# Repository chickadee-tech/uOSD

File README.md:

# Chickadee Tech Acro Polystack Mod #
This mod cradles a MicroMinimOSD and connects it to the base control board.

## Documentation ##
See the [wiki](https://github.com/chickadee-tech/uOSD/wiki) for documentation.

## Polystack ##
This **mod** board is part of the Polystack platform for modular microcontrol systems. More information on the platform can be found at [polystack.org](http://polystack.org).

## Support ##
If you need support with a board you own or have development questions please email support@chickadee.tech or check [chickadee.tech/support](https://chickadee.tech/support) for other ways to get support.

## Contributing ##
Please note that this project is released with a [Contributor Code of Conduct](CODE_OF_CONDUCT.md). By participating in this project you agree to abide by its terms.

### Setup ###
Components and footprints for PCB parts are not included in this repository. Instead, checkout the [chickadee-tech/kicad-libs](https://github.com/chickadee-tech/kicad-libs) repository in the same directory that this repository is checked out in. All part definitions should be relative so that they will load correctly.

### Pull requests ###
For fixes please submit a pull request to the original repository. After the pull request is merged, check the [Chickadee Tech Active Contributor Discount (ACD)](https://chickadee.tech/active-contributor) to see if you are eligible for a discount code to use on your next purchase.

### Derivatives ###
If developing your own version of the MicroMinimOSD cradle board please remove all Chickadee Tech trademarks and follow the [CC-BY license](LICENSE). While not required, please consider open sourcing your modifications so others can learn from your improvements. If you do email support@chickadee.tech and we may choose to add your project to the ACD.

You may also license the Polystack logo for free by emailing support@chickadee.tech. We'll ask for your gerbers to ensure the design complies with specifications laid out [here](https://github.com/chickadee-tech/polystack/wiki) and provide written permission to use the trademark after compliance has been demonstrated.

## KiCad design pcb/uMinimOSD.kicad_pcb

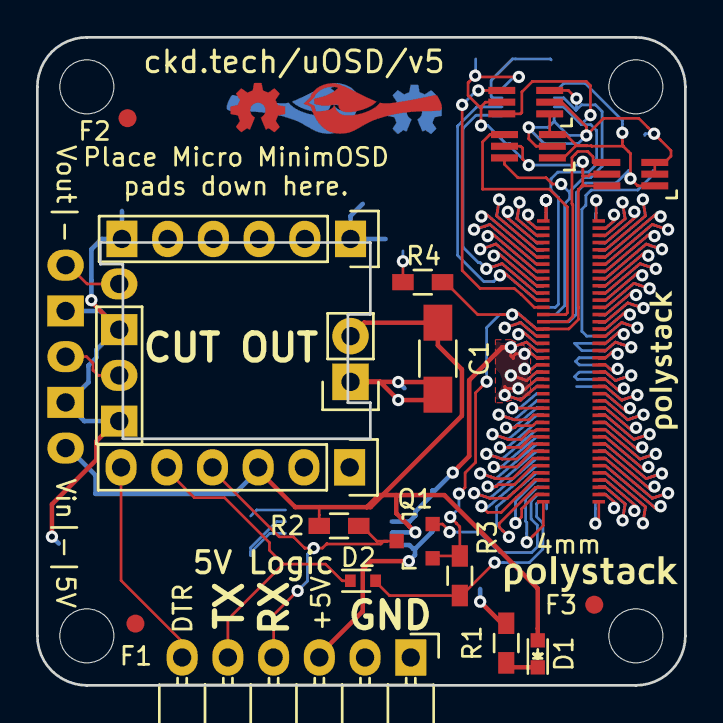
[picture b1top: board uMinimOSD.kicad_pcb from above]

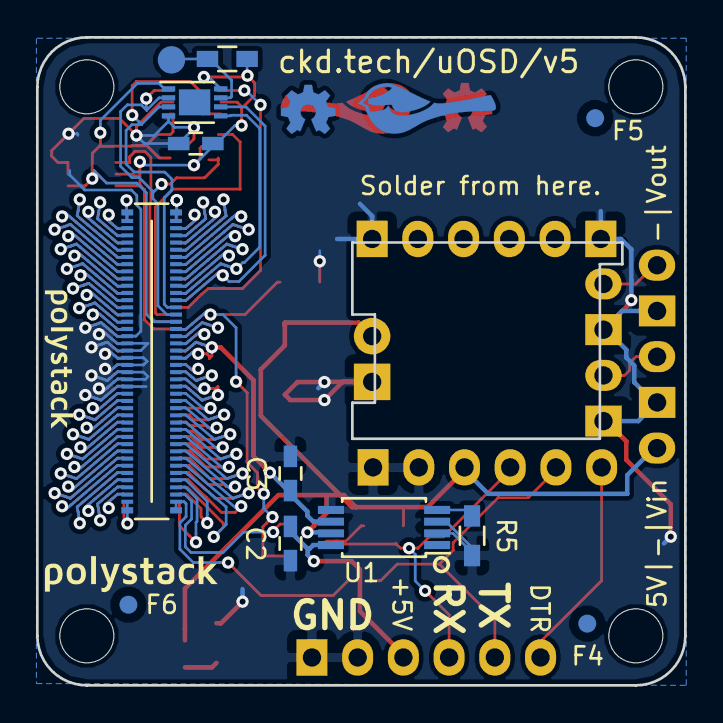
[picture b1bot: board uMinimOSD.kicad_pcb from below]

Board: 2 copper layers, 36.0 x 36.0 mm, 37 parts (14 on the bottom side), 81 nets.

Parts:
C1: 10uF; C_1206_HandSoldering
C2, C3: 0.1uF; C_0603_HandSoldering
D1: Red; LED-0603
D2: RB751S40; SOD-523
F1, F2, F3, F4, F5, F6: 1mm; Fiducial
P1: CONN_01X05; Pin_Header_Straight_1x05
P2: CONN_01X04; Pin_Header_Straight_1x04
P3, P4: CONN_01X06; Pin_Header_Straight_1x06
P5: CONN_01X02; Pin_Header_Straight_1x02
P6: CONN_01X06; Pin_Header_Angled_1x06
PORT_ANDOR1: SN74LVC1G0832; SC-70-6_Handsoldering
PORT_C1: 0.1uF; C_0603_HandSoldering
PORT_IC1: AT24CS02-MAHM; DFN-8-1EP_3x2mm_Pitch0.5mm
PORT_IN1: CKD_SANDWICH; DF40-80pin-Header
PORT_INV1: SN74LVC1G58; SC-70-6_Handsoldering
PORT_OUT1: CKD_SANDWICH; DF40-3-4mm-80pin-Receptacle
PORT_P1: CONN_01X01; Measurement_Point_Round-SMD-Pad_Small
PORT_R1: 10k; R_0603_HandSoldering
PORT_XOR1: SN74LVC1G58; SC-70-6_Handsoldering
Q1: Q_NMOS_GSD; SOT-23
R1: 1k; R_0603_HandSoldering
R2, R3, R4: 10k; R_0603_HandSoldering
R5: 470; R_0603_HandSoldering
U1: TPS2112; TSSOP-8_4.4x3mm_Pitch0.65mm
svg2mod, svg2mod#2: G***; polystack-bold-0.5
svg2mod#3, svg2mod#4: G***; polystack-bold-0.4

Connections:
+3V3: PORT_ANDOR1.5, PORT_C1.1, PORT_IC1.8, PORT_IN1.16, PORT_INV1.5, PORT_INV1.6, PORT_OUT1.16, PORT_R1.2, PORT_XOR1.5, Q1.1, R3.1, R4.1
+5V: C1.1, D1.2, P1.1, P3.3, P5.2, R2.1, U1.7
/DTR: P3.6, P6.6
/ExpansionPort/3V3_0.3A_E: PORT_IN1.17, PORT_OUT1.17
/ExpansionPort/+BATT: PORT_IN1.18, PORT_OUT1.18
/ExpansionPort/ADC1: PORT_IN1.49, PORT_OUT1.49
/ExpansionPort/ADC2: PORT_IN1.50, PORT_OUT1.50
/ExpansionPort/BOOT: PORT_IN1.65, PORT_OUT1.65
/ExpansionPort/CAN_HI: PORT_IN1.67, PORT_OUT1.67
/ExpansionPort/CAN_LO: PORT_IN1.68, PORT_OUT1.68
/ExpansionPort/FS_5V: C3.1, PORT_IN1.19, PORT_IN1.20, PORT_IN1.21, PORT_IN1.22, PORT_IN1.23, PORT_IN1.24, PORT_OUT1.19, PORT_OUT1.20, PORT_OUT1.21, PORT_OUT1.22, PORT_OUT1.23, PORT_OUT1.24, U1.6
/ExpansionPort/GPIO1: PORT_IN1.5, PORT_OUT1.5
/ExpansionPort/GPIO2: PORT_IN1.6, PORT_OUT1.6
/ExpansionPort/GPIO3: PORT_IN1.7, PORT_OUT1.7
/ExpansionPort/GPIO4: PORT_IN1.8, PORT_OUT1.8
/ExpansionPort/GPIO5: PORT_IN1.9, PORT_OUT1.9
/ExpansionPort/GPIO6: PORT_IN1.10, PORT_OUT1.10
/ExpansionPort/HEIGHT_1: PORT_ANDOR1.1, PORT_IC1.1, PORT_IN1.15, PORT_INV1.1, PORT_XOR1.1, PORT_XOR1.3
/ExpansionPort/HEIGHT_2: PORT_ANDOR1.3, PORT_IC1.2, PORT_IN1.14, PORT_XOR1.6
/ExpansionPort/HEIGHT_4: PORT_ANDOR1.6, PORT_IC1.3, PORT_IN1.13
/ExpansionPort/NEW_HEIGHT_1: PORT_INV1.4, PORT_OUT1.15
/ExpansionPort/NEW_HEIGHT_2: PORT_OUT1.14, PORT_XOR1.4
/ExpansionPort/NEW_HEIGHT_4: PORT_ANDOR1.4, PORT_OUT1.13
/ExpansionPort/RESET: PORT_IN1.66, PORT_OUT1.66
/ExpansionPort/SDMMC1_CK: PORT_IN1.55, PORT_OUT1.55
/ExpansionPort/SDMMC1_CMD: PORT_IN1.56, PORT_OUT1.56
/ExpansionPort/SDMMC1_D0: PORT_IN1.51, PORT_OUT1.51
/ExpansionPort/SDMMC1_D1: PORT_IN1.52, PORT_OUT1.52
/ExpansionPort/SDMMC1_D2: PORT_IN1.53, PORT_OUT1.53
/ExpansionPort/SDMMC1_D3: PORT_IN1.54, PORT_OUT1.54
/ExpansionPort/SPI1_MISO: PORT_IN1.79, PORT_OUT1.79
/ExpansionPort/SPI1_MOSI: PORT_IN1.80, PORT_OUT1.80
/ExpansionPort/SPI1_NSS: PORT_IN1.77, PORT_OUT1.77
/ExpansionPort/SPI1_SCK: PORT_IN1.78, PORT_OUT1.78
/ExpansionPort/SPI2_MISO: PORT_IN1.75, PORT_OUT1.75
/ExpansionPort/SPI2_MOSI: PORT_IN1.76, PORT_OUT1.76
/ExpansionPort/SPI2_NSS: PORT_IN1.73, PORT_OUT1.73
/ExpansionPort/SPI2_SCK: PORT_IN1.74, PORT_OUT1.74
/ExpansionPort/SPI3_MISO: PORT_IN1.71, PORT_OUT1.71
/ExpansionPort/SPI3_MOSI: PORT_IN1.72, PORT_OUT1.72
/ExpansionPort/SPI3_NSS: PORT_IN1.69, PORT_OUT1.69
/ExpansionPort/SPI3_SCK: PORT_IN1.70, PORT_OUT1.70
/ExpansionPort/TIM1: PORT_IN1.1, PORT_OUT1.1
/ExpansionPort/TIM2: PORT_IN1.2, PORT_OUT1.2
/ExpansionPort/TIM3: PORT_IN1.3, PORT_OUT1.3
/ExpansionPort/TIM4: PORT_IN1.4, PORT_OUT1.4
/ExpansionPort/TIMG1_CH1: PORT_IN1.41, PORT_OUT1.41
/ExpansionPort/TIMG1_CH2: PORT_IN1.42, PORT_OUT1.42
/ExpansionPort/TIMG1_CH3: PORT_IN1.43, PORT_OUT1.43
/ExpansionPort/TIMG1_CH4: PORT_IN1.44, PORT_OUT1.44
/ExpansionPort/TIMG2_CH1: PORT_IN1.45, PORT_OUT1.45
/ExpansionPort/TIMG2_CH2: PORT_IN1.46, PORT_OUT1.46
/ExpansionPort/TIMG2_CH3: PORT_IN1.47, PORT_OUT1.47
/ExpansionPort/TIMG2_CH4: PORT_IN1.48, PORT_OUT1.48
/ExpansionPort/UART1_RX: D2.2, PORT_IN1.40, R3.2
/ExpansionPort/UART1_TX: PORT_IN1.39, Q1.2
/ExpansionPort/UART2_RX: PORT_IN1.38, PORT_OUT1.40
/ExpansionPort/UART2_TX: PORT_IN1.37, PORT_OUT1.39
/ExpansionPort/UART3_RX: PORT_IN1.36, PORT_OUT1.38
/ExpansionPort/UART3_TX: PORT_IN1.35, PORT_OUT1.37
/ExpansionPort/UART4_RX: PORT_IN1.34, PORT_OUT1.36
/ExpansionPort/UART4_TX: PORT_IN1.33, PORT_OUT1.35
/ExpansionPort/UART5_RX: PORT_IN1.32, PORT_OUT1.34
/ExpansionPort/UART5_TX: PORT_IN1.31, PORT_OUT1.33
/ExpansionPort/UART6_RX: PORT_IN1.30, PORT_OUT1.32
/ExpansionPort/UART6_TX: PORT_IN1.29, PORT_OUT1.31
/ExpansionPort/UART7_RX: PORT_IN1.28, PORT_OUT1.30
/ExpansionPort/UART7_TX: PORT_IN1.27, PORT_OUT1.29
/ExpansionPort/UART8_RX: PORT_IN1.26, PORT_OUT1.28
/ExpansionPort/UART8_TX: PORT_IN1.25, PORT_OUT1.27
/ExpansionPort/i2c_SCL: PORT_IC1.6, PORT_IN1.12, PORT_OUT1.12
/ExpansionPort/i2c_SDA: PORT_IC1.5, PORT_IN1.11, PORT_OUT1.11
/FTDI_5V: C2.1, P6.3, U1.8
/RX: D2.1, P3.5, P6.5
/TX: P3.4, P6.4, Q1.3, R2.2
/Vin: P1.3, P2.3
/Vout: P1.5, P2.1
GNDPWR: C1.2, C2.2, C3.2, P1.2, P1.4, P2.2, P2.4, P3.1, P3.2, P4.1, P4.6, P5.1, P6.1, P6.2, PORT_ANDOR1.2, PORT_C1.2, PORT_IC1.4, PORT_IN1.57, PORT_IN1.58, PORT_IN1.59, PORT_IN1.60, PORT_IN1.61, PORT_IN1.62, PORT_IN1.63, PORT_IN1.64, PORT_INV1.2, PORT_INV1.3, PORT_OUT1.57, PORT_OUT1.58, PORT_OUT1.59, PORT_OUT1.60, PORT_OUT1.61, PORT_OUT1.62, PORT_OUT1.63, PORT_OUT1.64, PORT_XOR1.2, R1.2, R4.2, R5.2, U1.2, U1.3, U1.5
unnamed: D1.1, R1.1
unnamed: PORT_IC1.7, PORT_P1.1, PORT_R1.1
unnamed: R5.1, U1.4

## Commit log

2016-01-07 v1 of a Micro Minim OSD cradle.
2016-02-06 v2 of uMinimOSD which corrects RX and TX and also makes it available in ftdi form.
2016-04-07 Correct pinout of power or IC.
2016-04-13 Rebrand everything to Polystack and increment versions.
2016-04-16 Final gerbers for test manufacturing run.
2016-06-07 Remove extra chickadee logo, pdate polystack logo to bold variant, connect i2c lines to eeprom and bump version number.
2016-07-07 Add license information to many files. PCB design files are CC-BY and code is MIT license.
2016-07-07 Add back .gitignore after repo split.
2016-07-07 Convert to relative component and footprint paths.

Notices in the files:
pcb/uMinimOSD.kicad_pcb:
Copyright 2016 Chickadee Tech LLC,
This work is licensed under the Creative Commons Attribution 4.0 International License.
To view a copy of this license, visit http://creativecommons.org/licenses/by/4.0
or send a letter to Creative Commons, PO Box 1866, Mountain View, CA 94042, USA.
